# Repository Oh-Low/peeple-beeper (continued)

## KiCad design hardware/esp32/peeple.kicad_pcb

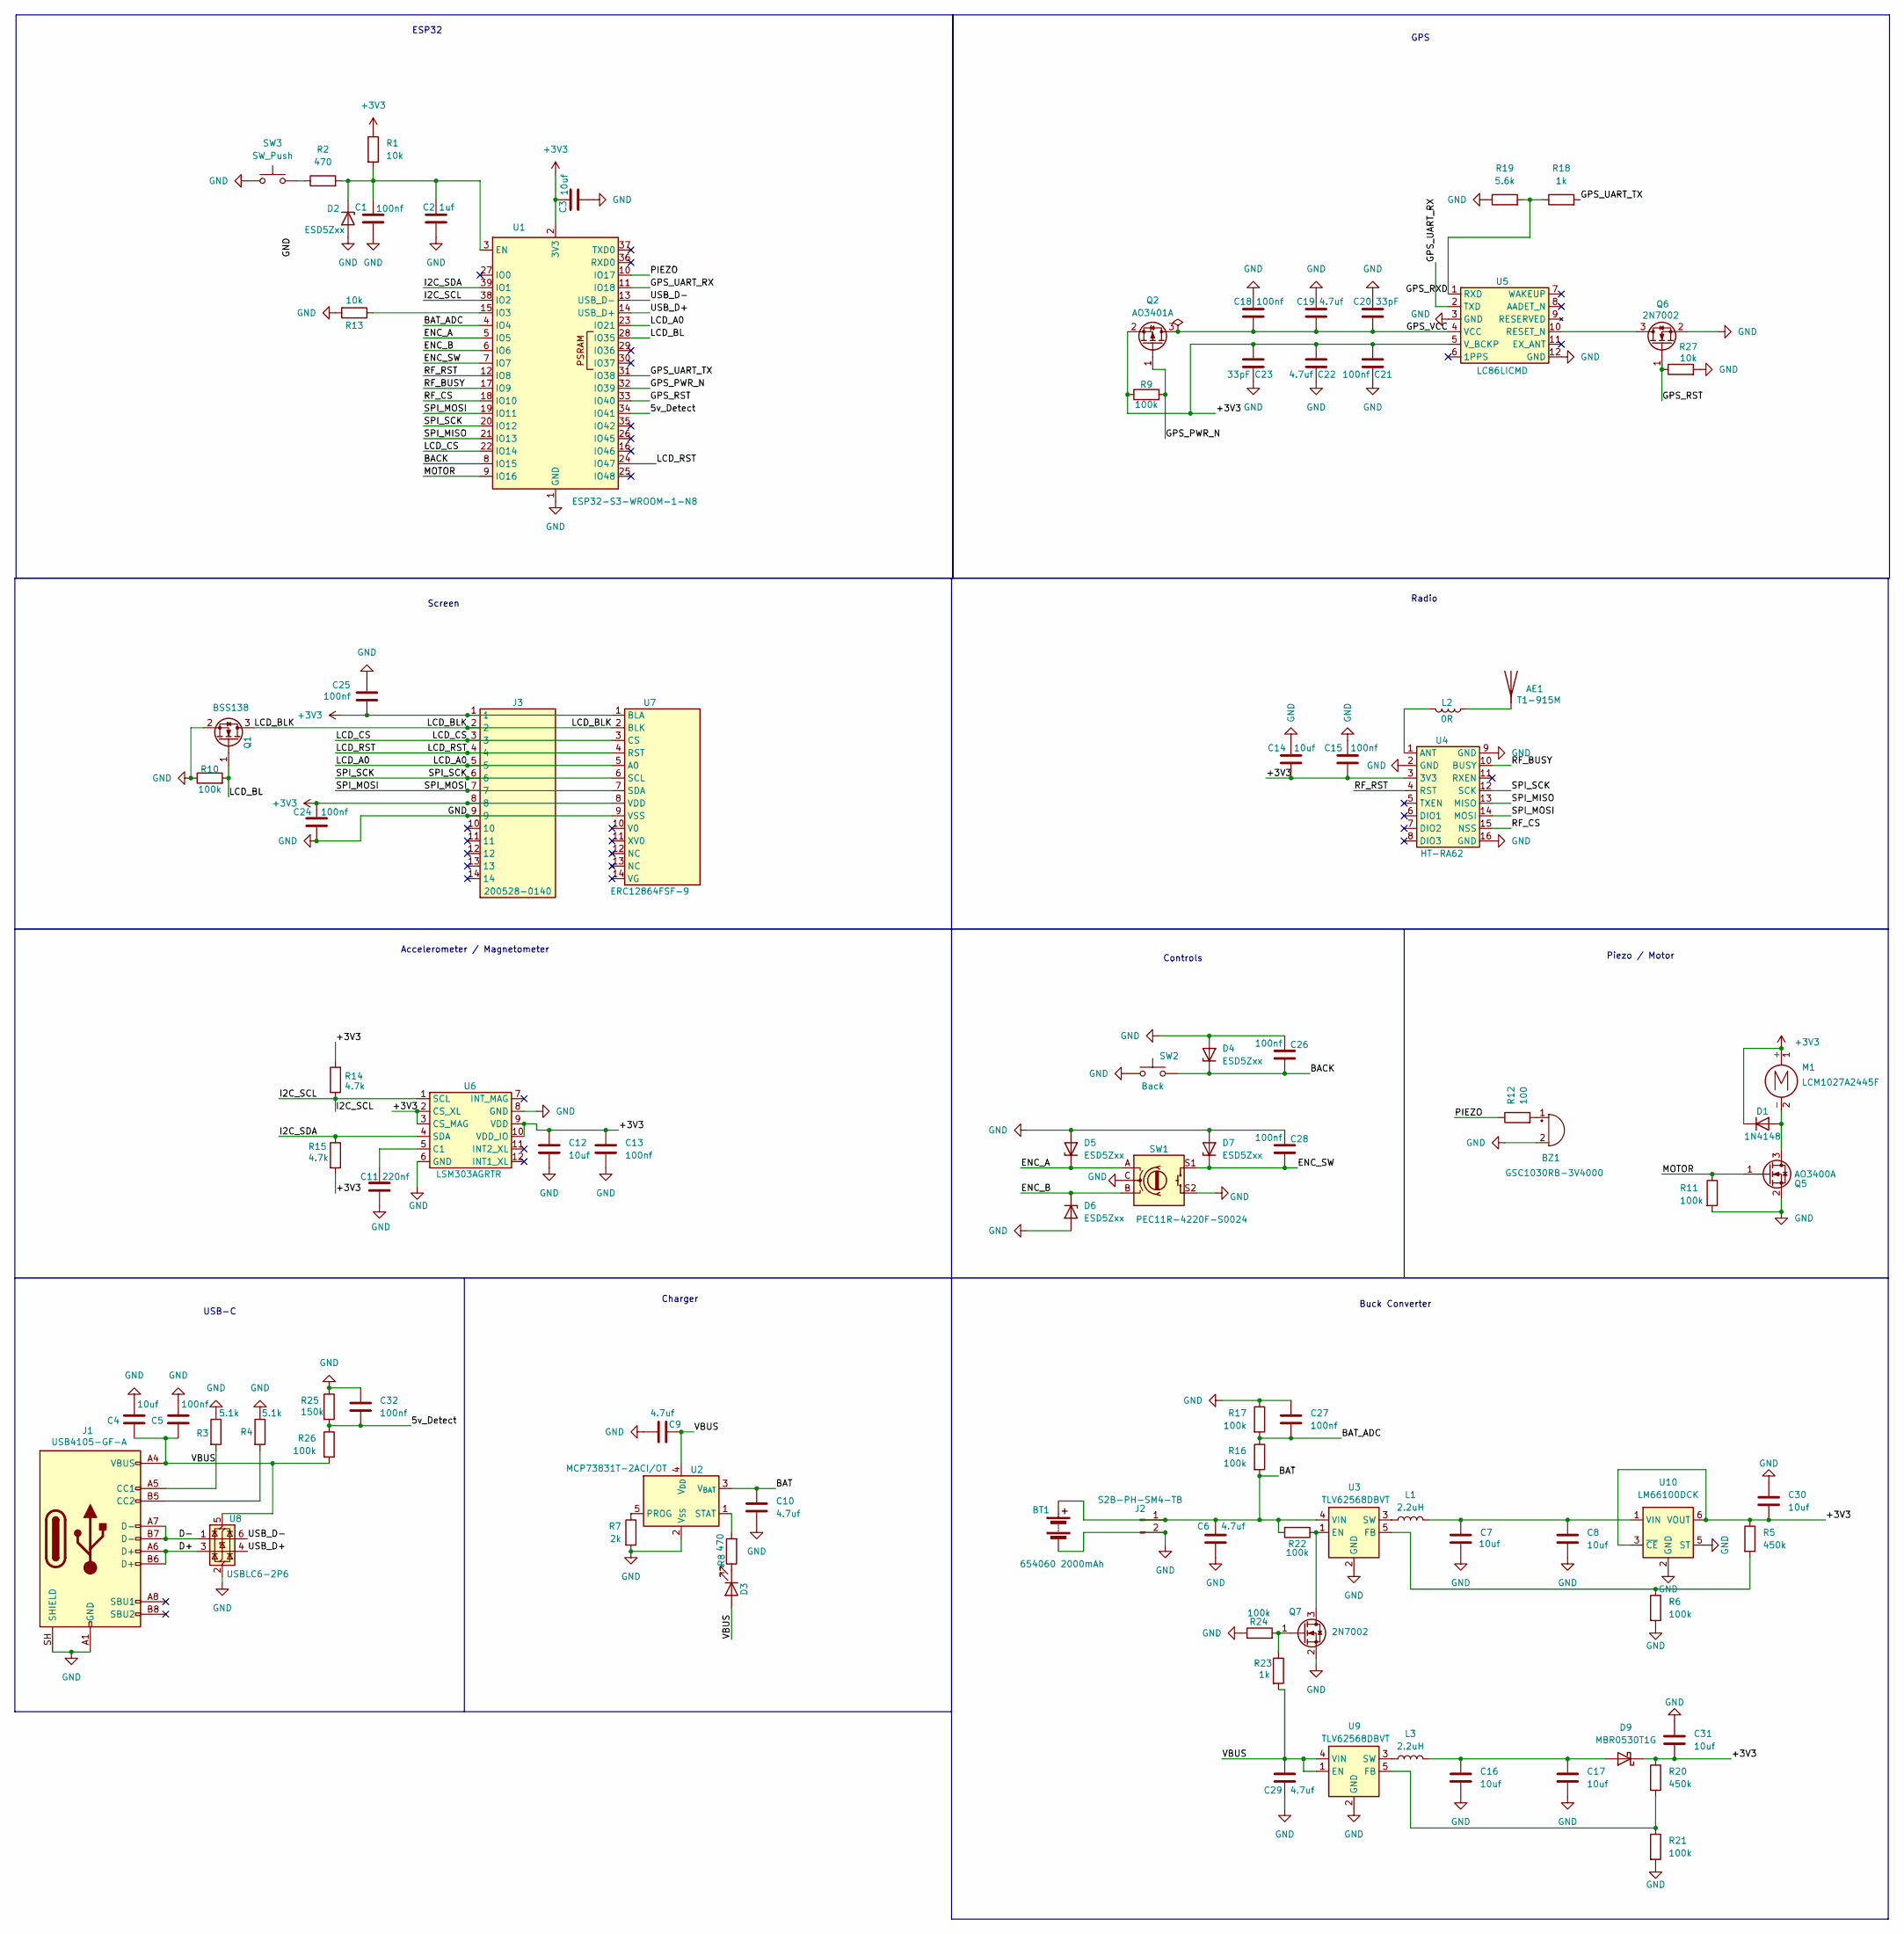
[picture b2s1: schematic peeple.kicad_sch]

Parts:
AE1: T1-915M
BT1: 654060 2000mAh; MPN LA123150
BZ1: GSC1030RB-3V4000; Piezo_10x10
C1, C5, C13, C15: 100nf
C2: 1uf
C3, C4, C7, C8, C12, C14: 10uf
C6, C9, C10: 4.7uf
C11: 220nf
C16, C17, C30, C31: 10uf; C_0805_2012Metric
C18, C21, C24, C25, C26, C27, C28, C32: 100nf; C_0603_1608Metric
C19, C22, C29: 4.7uf; C_0805_2012Metric
C20, C23: 33pF; C_0603_1608Metric
D1: 1N4148; D_SOD-123
D2, D4, D5, D6, D7: ESD5Zxx; D_SOD-523
D3: LED; LED_0603_1608Metric
D9: MBR0530T1G; D_SOD-123; MPN MBR0530T1G; DigiKey_PN MBR0530T1GOSCT-ND
J1: USB4105-GF-A; USB_C_Receptacle_GCT_USB4105-xx-A_16P_TopMnt_Horizontal
J2: S2B-PH-SM4-TB; JST_PH_S2B-PH-SM4-TB_1x02-1MP_P2.00mm_Horizontal
J3: 200528-0140; Molex_200528-0140_1x14-1MP_P1.00mm_Horizontal
L1: 2.2uH
L2: 0R; R_0603_1608Metric
L3: 2.2uH; L_1210_3225Metric
M1: LCM1027A2445F; Motor_Coin_10mm
Q1: BSS138; SOT-23
Q2: AO3401A; SOT-23
Q5: AO3400A; SOT-23; MPN AO3400A
Q6, Q7: 2N7002; SOT-23
R1, R13: 10k
R2, R8: 470
R3: 5.1k
R4: 5.1k; R_0603_1608Metric
R5: 450k; R_0603_1608Metric
R6, R9, R10, R16, R17, R21, R22: 100k
R7: 2k
R11, R24, R26: 100k; R_0603_1608Metric
R12: 100; R_0603_1608Metric
R14, R15: 4.7k
R18: 1k
R19: 5.6k
R20: 450k
R23: 1k; R_0603_1608Metric
R25: 150k; R_0603_1608Metric
R27: 10k; R_0603_1608Metric
SW1: PEC11R-4220F-S0024; RotaryEncoder_Alps_EC11E-Switch_Vertical_H20mm
SW2: Back; SW_SPST_TL3305A
SW3: SW_Push; SW_SPST_TL3305A
U1: ESP32-S3-WROOM-1-N8; ESP32-S3-WROOM-1
U2: MCP73831T-2ACI/OT; SOT-23-5
U3, U9: TLV62568DBVT; SOT-23-5
U4: HT-RA62
U5: LC86LICMD
U6: LSM303AGRTR; LGA-12_2x2mm_P0.5mm
U7: ERC12864FSF-9
U8: USBLC6-2P6; SOT-666
U10: LM66100DCK; SOT-363_SC-70-6

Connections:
+3V3: C3.1, C12.1, C13.1, C14.2, C15.2, C21.2, C22.2, C23.2, C24.1, C25.2, C30.1, C31.1, D1.1 (K), D9.1 (K), J3.1, J3.8, M1.1 (+), Q2.2 (S), R1.1, R5.1, R9.1, R14.1, R15.2, R20.1, U1.2 (3V3), U4.3 (3V3), U5.5 (V_BCKP), U6.2 (CS_XL), U6.3 (CS_MAG), U6.9 (VDD), U6.10 (VDD_IO), U7.1 (BLA), U7.8 (VDD), U10.3 (~CE), U10.6 (VOUT)
/5v_Detect: C32.2, R25.2, R26.1, U1.34 (IO41)
/BACK: C26.2, D4.1 (K), SW2.2, U1.8 (IO15)
/BAT: BT1.1 (+), C6.1, C10.1, J2.1, R16.2, R22.2, U2.3 (V_{BAT}), U3.4 (VIN)
/BAT_ADC: C27.2, R16.1, R17.2, U1.4 (IO4)
/D+: J1.A6 (D+), J1.B6 (D+), U8.3 (I/O2)
/D-: J1.A7 (D-), J1.B7 (D-), U8.1 (I/O1)
/ENC_A: D5.1 (K), SW1.A, U1.5 (IO5)
/ENC_B: D6.1 (K), SW1.B, U1.6 (IO6)
/ENC_SW: C28.2, D7.1 (K), SW1.S1, U1.7 (IO7)
/GPS_PWR_N: Q2.1 (G), R9.2, U1.32 (IO39)
/GPS_RST: Q6.1 (G), R27.1, U1.33 (IO40)
/GPS_RXD: R18.1, R19.2, U5.1 (RXD)
/GPS_UART_RX: U1.11 (IO18), U5.2 (TXD)
/GPS_UART_TX: R18.2, U1.31 (IO38)
/GPS_VCC: C18.2, C19.2, C20.2, Q2.3 (D), U5.4 (VCC)
/I2C_SCL: R14.2, U1.38 (IO2), U6.1 (SCL)
/I2C_SDA: R15.1, U1.39 (IO1), U6.4 (SDA)
/LCD_A0: J3.5, U1.23 (IO21), U7.5 (A0)
/LCD_BL: Q1.1 (G), R10.2, U1.28 (IO35)
/LCD_BLK: J3.2, Q1.3 (D), U7.2 (BLK)
/LCD_CS: J3.3, U1.22 (IO14), U7.3 (CS)
/LCD_RST: J3.4, U1.24 (IO47), U7.4 (RST)
/MOTOR: Q5.1 (G), R11.1, U1.9 (IO16)
/PIEZO: R12.1, U1.10 (IO17)
/RF_BUSY: U1.17 (IO9), U4.10 (BUSY)
/RF_CS: U1.18 (IO10), U4.15 (NSS)
/RF_RST: U1.12 (IO8), U4.4 (RST)
/SPI_MISO: U1.21 (IO13), U4.13 (MISO)
/SPI_MOSI: J3.7, U1.19 (IO11), U4.14 (MOSI), U7.7 (SDA)
/SPI_SCK: J3.6, U1.20 (IO12), U4.12 (SCK), U7.6 (SCL)
/USB_D+: U1.14 (USB_D+), U8.4 (I/O2)
/USB_D-: U1.13 (USB_D-), U8.6 (I/O1)
/VBUS: C4.2, C5.2, C9.1, C29.1, D3.2 (A), J1.A4 (VBUS), J1.A9 (VBUS), J1.B4 (VBUS), J1.B9 (VBUS), R23.2, R26.2, U2.4 (V_{DD}), U8.5 (VBUS), U9.1 (EN), U9.4 (VIN)
GND: BT1.2 (-), BZ1.2 (-), C1.2, C2.2, C3.2, C4.1, C5.1, C6.2, C7.2, C8.2, C9.2, C10.2, C11.1, C12.2, C13.2, C14.1, C15.1, C16.2, C17.2, C18.1, C19.1, C20.1, C21.1, C22.1, C23.1, C24.2, C25.1, C26.1, C27.1, C28.1, C29.2, C30.2, C31.2, C32.1, D2.2 (A), D4.2 (A), D5.2 (A), D6.2 (A), D7.2 (A), J1.A1 (GND), J1.A12 (GND), J1.B1 (GND), J1.B12 (GND), J1.SH (SHIELD), J2.2, J3.9, Q1.2 (S), Q5.2 (S), Q6.2 (S), Q7.2 (S), R3.1, R4.1, R6.2, R7.2, R10.1, R11.2, R13.2, R17.1, R19.1, R21.2, R24.1, R25.1, R27.2, SW1.C, SW1.S2, SW2.1, SW3.1, U1.1 (GND), U1.40 (GND), U1.41 (GND), U2.2 (V_{SS}), U3.2 (GND), U4.2 (GND), U4.9 (GND), U4.16 (GND), U5.3 (GND), U5.12 (GND), U6.6 (GND), U6.8 (GND), U7.9 (VSS), U8.2 (GND), U9.2 (GND), U10.2 (GND), U10.5 (ST)
unnamed: AE1.1 (A_1), L2.1
unnamed: BZ1.1 (+), R12.2
unnamed: D1.2 (A), M1.2 (-), Q5.3 (D)
unnamed: C1.1, C2.1, D2.1 (K), R1.2, R2.2, U1.3 (EN)
unnamed: D3.1 (K), R8.1
unnamed: C16.1, C17.1, D9.2 (A), L3.2
unnamed: J1.A5 (CC1), R3.2
unnamed: J1.B5 (CC2), R4.2
unnamed: Q6.3 (D), U5.10 (RESET_N)
unnamed: Q7.3 (D), R22.1, U3.1 (EN)
unnamed: Q7.1 (G), R23.1, R24.2
unnamed: R2.1, SW3.2
unnamed: R13.1, U1.15 (IO3)
unnamed: R7.1, U2.5 (PROG)
unnamed: R8.2, U2.1 (STAT)
unnamed: R5.2, R6.1, U3.5 (FB)
unnamed: L1.1, U3.3 (SW)
unnamed: L2.2, U4.1 (ANT)
unnamed: C11.2, U6.5 (C1)
unnamed: R20.2, R21.1, U9.5 (FB)
unnamed: L3.1, U9.3 (SW)
unnamed: C7.1, C8.1, L1.2, U10.1 (VIN)

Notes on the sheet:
Controls
Charger
Accelerometer / Magnetometer
Buck Converter
Piezo / Motor
Screen
ESP32
USB-C
Radio
GPS

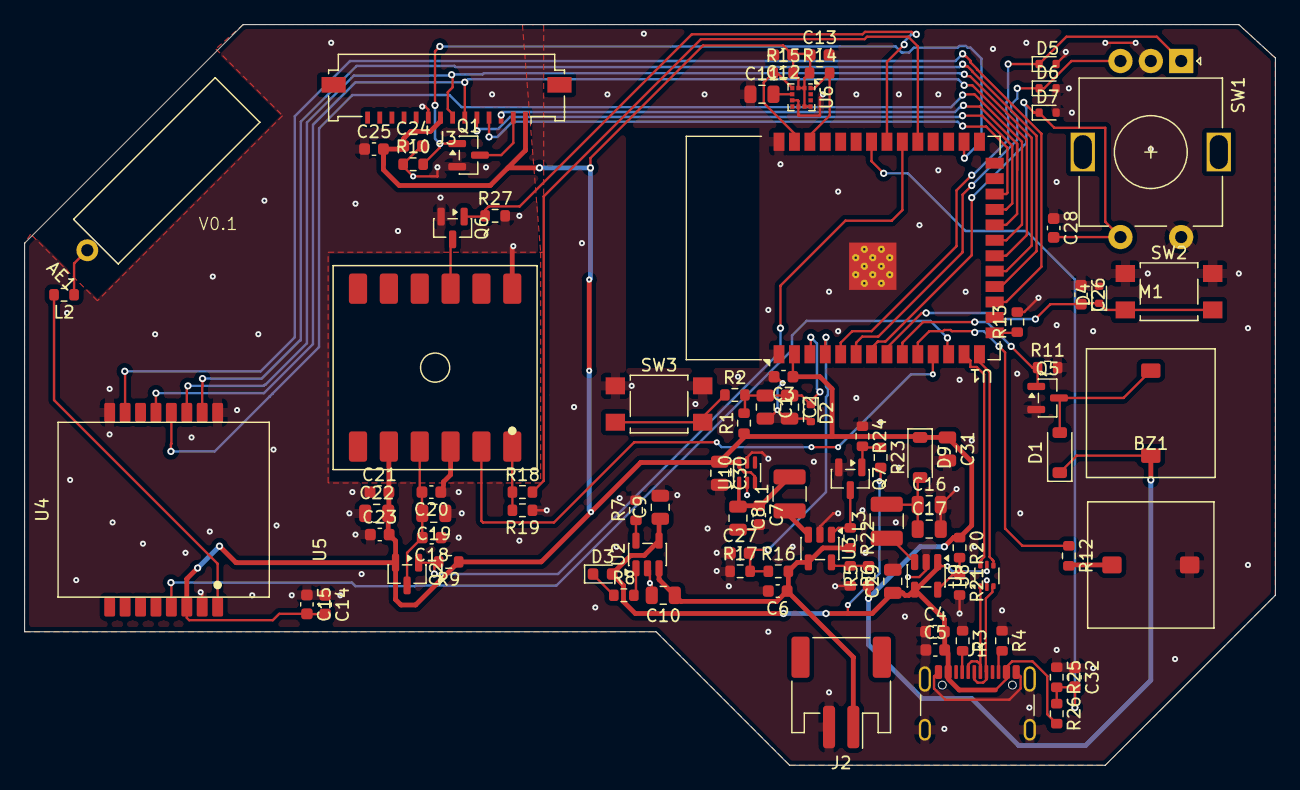
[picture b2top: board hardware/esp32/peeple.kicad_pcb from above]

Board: 2 copper layers, 103.0 x 61.0 mm, 93 parts (0 on the bottom side), 57 nets.

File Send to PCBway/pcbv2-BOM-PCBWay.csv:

Item,Designator,Qty,Manufacturer,Mfg Part #,Package/Footprint,Type,Value/Description
1,BZ1,1,INGHAi,C255330,Piezo_10x10,SMD,GSC1030RB-3V4000
2,C1,1,,,C_0805_2012Metric,SMD,Capacitor 100nf
3,C11,1,,,C_0805_2012Metric,SMD,Capacitor 220nf
4,"C3,C4,C7,C12,C14",5,,,C_0603_1608Metric,SMD,Capacitor 10uf
5,"C8,C16,C17,C30,C31",5,,,C_0805_2012Metric,SMD,Capacitor 10uf
6,"C9,C10,C19,C22,C29",5,,,C_0805_2012Metric,SMD,Capacitor 4.7uf
7,C2,1,,,C_0805_2012Metric,SMD,Capacitor 1uf
8,"C20,C23",2,,,C_0603_1608Metric,SMD,Capacitor 33pF
9,"C5,C13,C15,C18,C21,C24,C25,C26,C27,C28,C32",11,,,C_0603_1608Metric,SMD,Capacitor 100nf
10,C6,1,,,C_0603_1608Metric,SMD,Capacitor 4.7uf
11,D1,1,,1N4148W-7-F,D_SOD-123,SMD,1N4148 SOD-123
12,D3,1,,,LED_0603_1608Metric,SMD,LED Red 0603
13,"D2,D4,D5,D6,D7",5,onsemi,ESD5Z3.3T1GOSCT-ND,D_SOD-523,SMD,ESD5Z3.3T1G (ESD5Zxx)
14,D9,1,onsemi,MBR0530T1GOSCT-ND,D_SOD-123,SMD,MBR0530T1G
15,J1,1,GCT,2073-USB4105-GF-ACT-ND,USB_C_Receptacle_GCT_USB4105-xx-A_16P_TopMnt_Horizontal,SMD,USB4105-GF-A
16,J2,1,JST,455-1749-1-ND,JST_PH_S2B-PH-SM4-TB_1x02-1MP_P2.00mm_Horizontal,SMD,S2B-PH-SM4-TB(LF)(SN) (S2B-PH-SM4-TB)
17,J3,1,Molex,200528-0140,Molex_200528-0140_1x14-1MP_P1.00mm_Horizontal,SMD,200528-0140
18,"L1,L3",2,,,L_1210_3225Metric,SMD,Inductor/jumper 2.2uH
19,L2,1,,,R_0603_1608Metric,SMD,0R jumper 0603
20,M1,1,Leader,C2759984,Motor_Coin_10mm,SMD,LCM1027A2445F
21,Q1,1,,BSS138,SOT-23,SMD,BSS138
22,Q2,1,Alpha & Omega,C15127,SOT-23,SMD,AO3401A
23,Q5,1,Alpha & Omega,C20917,SOT-23,SMD,AO3400A
24,"Q6,Q7",2,,2N7002,SOT-23,SMD,2N7002
25,"R1,R13,R27",3,,,R_0603_1608Metric,SMD,Resistor 10k
26,R12,1,,,R_0603_1608Metric,SMD,Resistor 100
27,"R14,R15",2,,,R_0603_1608Metric,SMD,Resistor 4.7k
28,R19,1,,,R_0603_1608Metric,SMD,Resistor 5.6k
29,"R5,R20",2,,,R_0603_1608Metric,SMD,Resistor 450k
30,"R18,R23",2,,,R_0603_1608Metric,SMD,Resistor 1k
31,R25,1,,,R_0603_1608Metric,SMD,Resistor 150k
32,"R3,R4",2,,,R_0603_1608Metric,SMD,Resistor 5.1k
33,"R6,R9,R10,R11,R16,R17,R21,R22,R24,R26",10,,,R_0603_1608Metric,SMD,Resistor 100k
34,R7,1,,,R_0603_1608Metric,SMD,Resistor 2k
35,"R2,R8",2,,,R_0603_1608Metric,SMD,Resistor 470
36,"SW2,SW3",2,E-Switch,EG5626CT-ND,SW_SPST_TL3305A,SMD,TL3305AF160QG (Back)
37,U1,1,Espressif,C2913198,ESP32-S3-WROOM-1,SMD,ESP32-S3-WROOM-1-N8
38,U10,1,Texas Instruments,296-53541-1-ND,SOT-363_SC-70-6,SMD,LM66100DCKR (LM66100DCK)
39,U2,1,Microchip,MCP73831T-2ACI/OTCT-ND,SOT-23-5,SMD,MCP73831T-2ACI/OT
40,"U3,U9",2,Texas Instruments,C2864104,SOT-23-5,SMD,TLV62568DBVT
41,U4,1,Heltec,ZC-144-915,HT-RA62,SMD,HT-RA62
42,U5,1,Quectel,C7431213,LC86LICMD,SMD,LC86LICMD
43,U6,1,ST,C126671,LGA-12_2x2mm_P0.5mm,SMD,LSM303AGRTR
44,U8,1,ST,497-5026-1-ND,SOT-666,SMD,USBLC6-2P6
45,AE1,1,DreamLNK,C726086,T1-915M,THT,T1-915M
46,SW1,1,Bourns,PEC11R-4220F-S0024-ND,RotaryEncoder_Alps_EC11E-Switch_Vertical_H20mm,THT,PEC11R-4220F-S0024
